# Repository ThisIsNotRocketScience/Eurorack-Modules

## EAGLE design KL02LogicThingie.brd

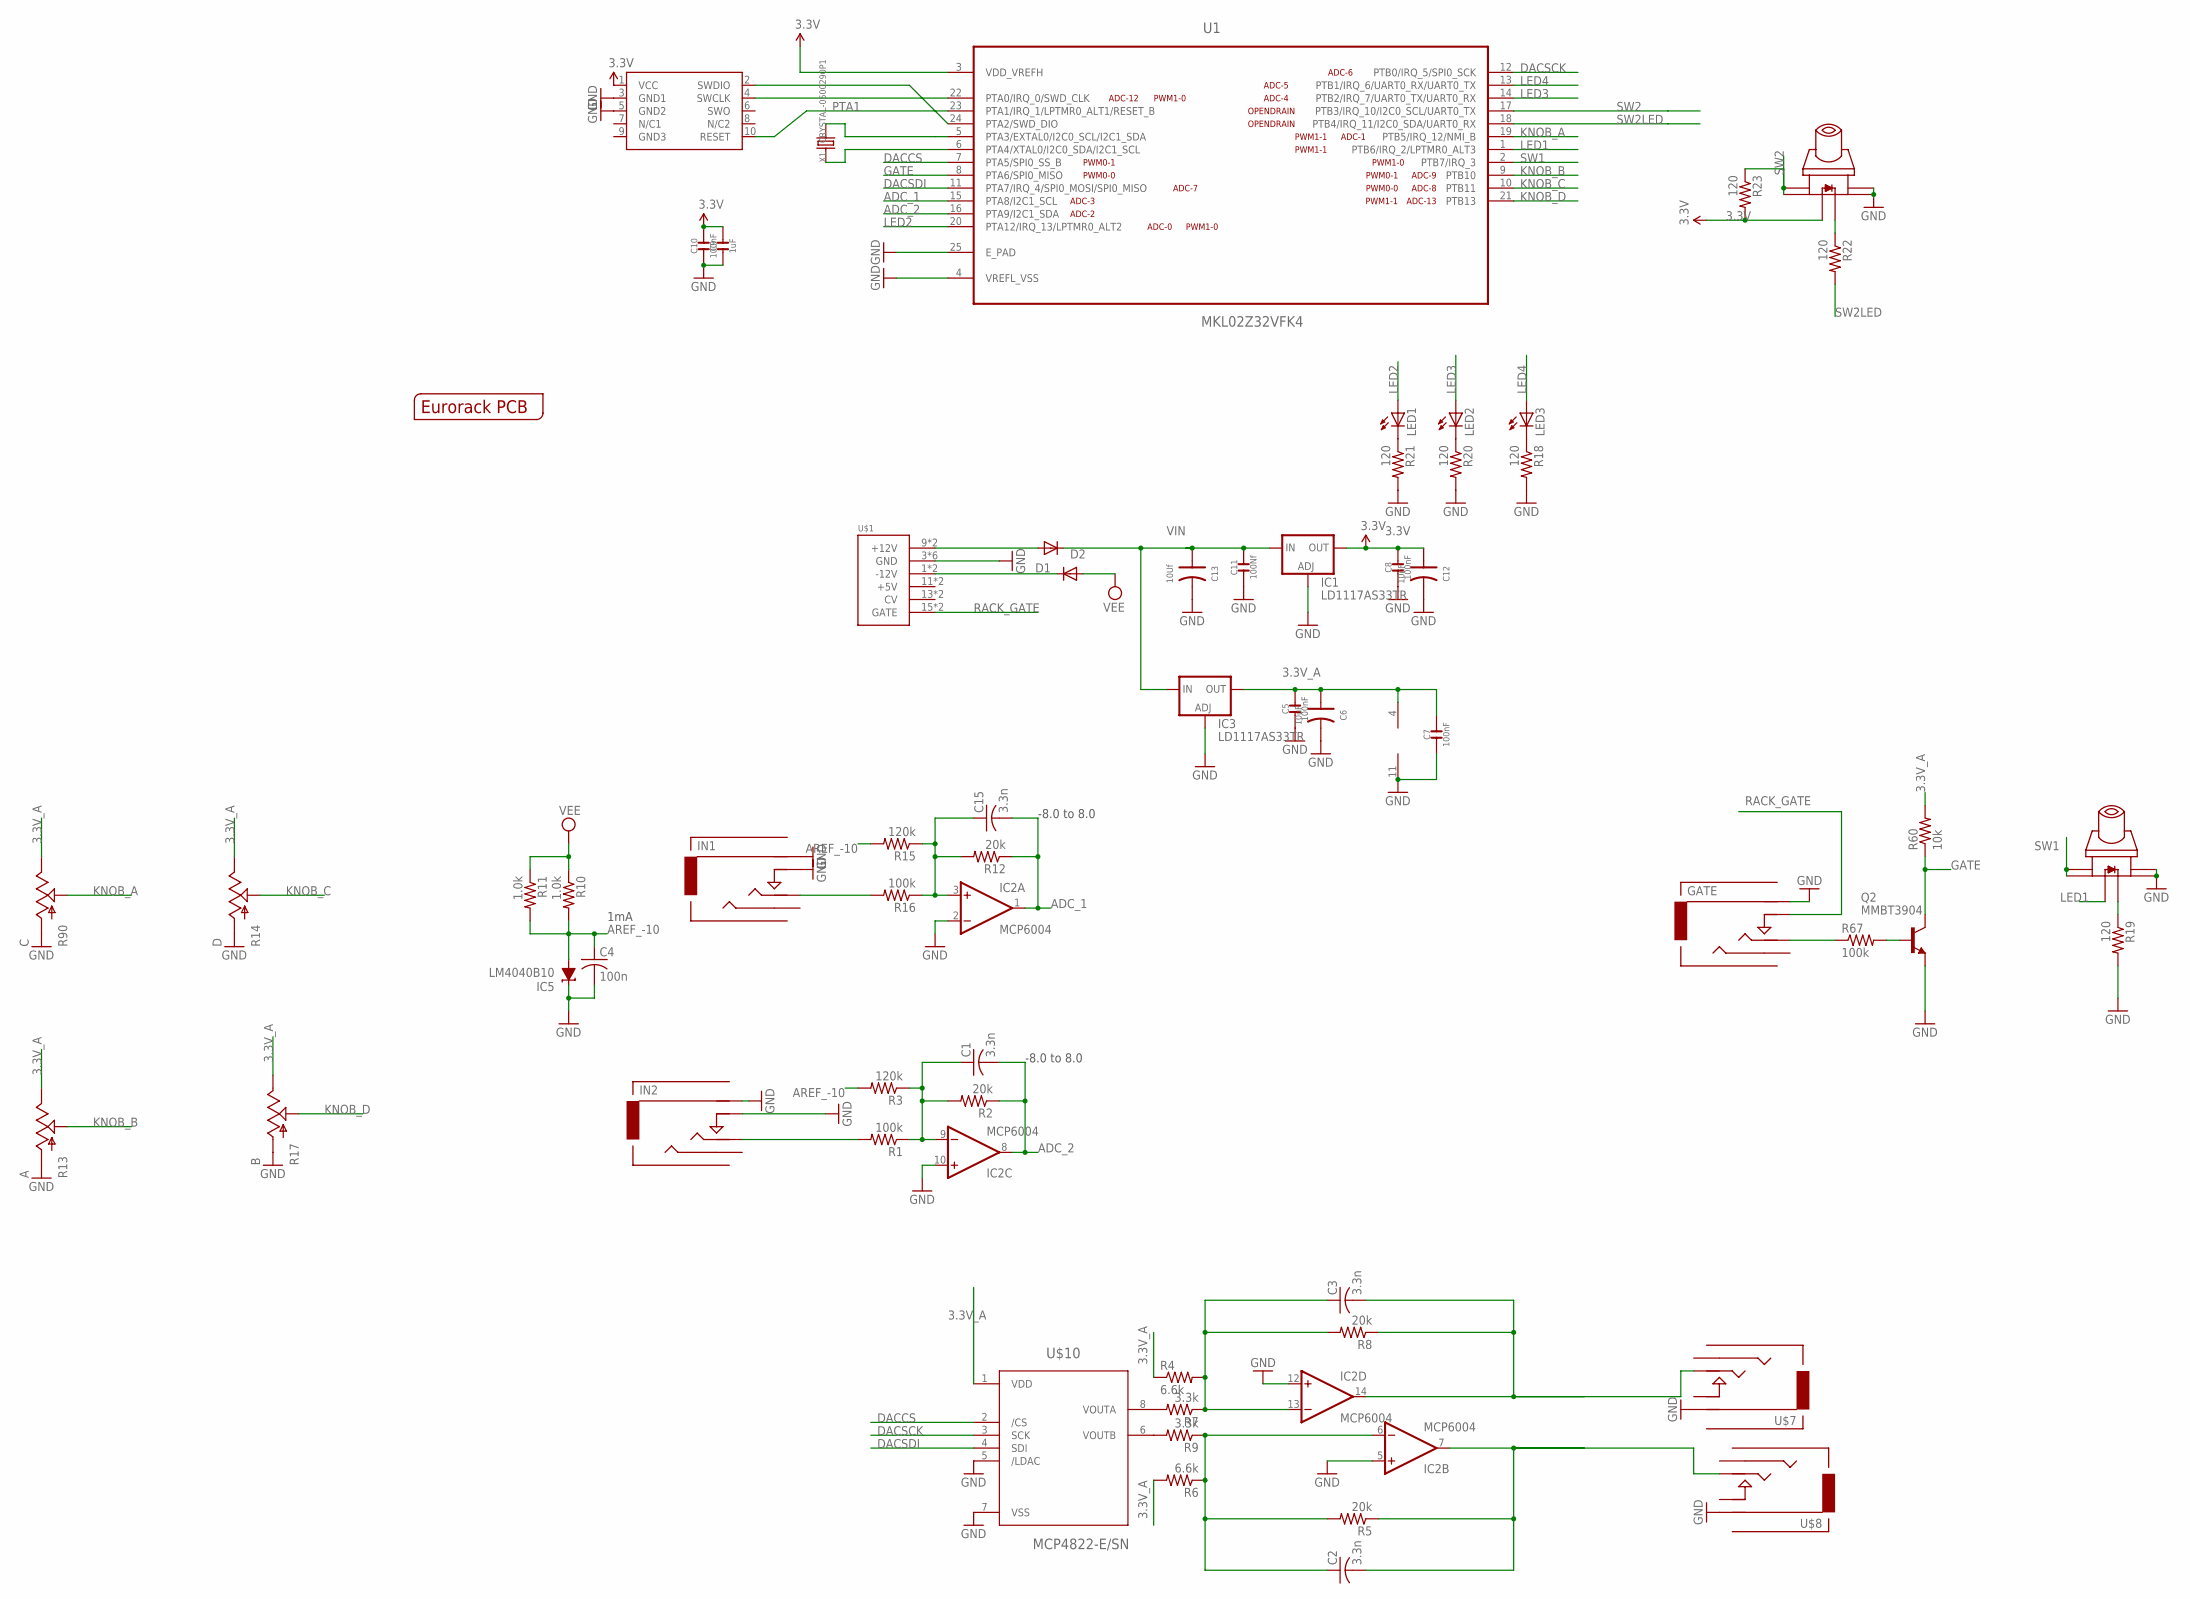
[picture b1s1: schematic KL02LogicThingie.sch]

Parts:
C1, C2, C3, C15: 3.3n; C0603
C4: 100n; C0603
C5, C7, C8, C10: 100nF; C0603
C6, C12: 10uF; AVX-A
C9: 1uF; C0603
C11: 100Nf; C0603
C13: 10Uf; AVX-A
D1, D2: 1N5819HW; SOD123
GATE: Gate; 3.5MM-JACK-SWITCH-13MM-INPUT
IC1, IC3: LD1117AS33TR; SOT223
IC2: MCP6004; SO14
IC5: LM4040B10; DBZ_R-PDSO-G3
IN1: In 2; 3.5MM-JACK-SWITCH-13MM-INPUT
IN2: In 1; 3.5MM-JACK-SWITCH-13MM-INPUT
LED1, LED2, LED3: LED3MM
Q2: MMBT3904; SOT23-BEC
R1, R16, R67: 100k; R0603
R2, R5, R8, R12: 20k; R0603
R3, R15: 120k; R0603
R4, R6: 6.6k; R0603
R7, R9: 3.3k; R0603
R10, R11: 1.0k; R0603
R13: A; OG-POTS_ALPS_POT_VERTICAL
R14: D; OG-POTS_ALPS_POT_VERTICAL
R17: B; OG-POTS_ALPS_POT_VERTICAL
R18, R19, R20, R21, R22, R23: 120; R0603
R60: 10k; R0603
R90: C; OG-POTS_ALPS_POT_VERTICAL
SWD1: CORTEX_SWD; M50-3600542
U1: MKL02Z32VFK4; QFN50P400X400X100-25N
U$1: POWER; POWER_16
U$2: EURORACK_PCB8HP; EURORACK8HPPCB
U$3, U$6: SWITCH_W_LED_PB6149L-X-102WHITE; PB6149L
U$7: Out 2; 3.5MM-JACK-SWITCH-13MM-OUTPUT
U$8: Out 1; 3.5MM-JACK-SWITCH-13MM-OUTPUT
U$10: MCP4822-E/SN; SOIC8-N_MC
X1: CRYSTAL-0500290P1; 2P-SMD-5.0X3.2

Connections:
3.3V: C8.2, C9.2, C10.2, C12.+ (1), IC1.2 (OUT), IC1.4 (OUT), R23.2, SWD1.1 (VCC), U1.3 (VDD_VREFH), U$3.LEDPOS (POS)
3.3V_A: C5.2, C6.+ (1), C7.2, IC2.4 (V+), IC3.2 (OUT), IC3.4 (OUT), R4.1, R6.2, R13.P$1 (E), R14.P$1 (E), R17.P$1 (E), R60.2, R90.P$1 (E), U$10.1 (VDD)
ADC_1: C15.2, IC2.1 (OUT), R12.1, U1.15 (PTA8/I2C1_SCL)
ADC_2: C1.2, IC2.8 (OUT), R2.1, U1.16 (PTA9/I2C1_SDA)
AREF_-10: C4.1, IC5.2 (A), R3.2, R10.2, R11.2, R15.2
DACCS: U1.7 (PTA5/SPI0_SS_B), U$10.2 (/CS)
DACSCK: U1.12 (PTB0/IRQ_5/SPI0_SCK), U$10.3 (SCK)
DACSDI: U1.11 (PTA7/IRQ_4/SPI0_MOSI/SPI0_MISO), U$10.4 (SDI)
GATE: Q2.C, R60.1, U1.8 (PTA6/SPI0_MISO)
GND: C4.2, C5.1, C6.- (2), C7.1, C8.1, C9.1, C10.1, C11.1, C12.- (2), C13.- (2), GATE.RING@1 (RING), GATE.RING@2 (RING), IC1.1 (ADJ), IC2.2 (-IN), IC2.5 (+IN), IC2.10 (+IN), IC2.11 (V-), IC2.12 (+IN), IC3.1 (ADJ), IC5.1 (C), IN1.RING@1 (RING), IN1.RING@2 (RING), IN1.SWITCH@1 (SWITCH), IN1.SWITCH@2 (SWITCH), IN2.RING@1 (RING), IN2.RING@2 (RING), IN2.SWITCH@1 (SWITCH), IN2.SWITCH@2 (SWITCH), Q2.E, R13.P$3 (A), R14.P$3 (A), R17.P$3 (A), R18.2, R19.2, R20.2, R21.2, R90.P$3 (A), SWD1.3 (GND1), SWD1.5 (GND2), U1.4 (VREFL_VSS), U1.25 (E_PAD), U$1.3 (GND), U$1.4 (GND), U$1.5 (GND), U$1.6 (GND), U$1.7 (GND), U$1.8 (GND), U$3.3, U$3.4, U$6.3, U$6.4, U$7.RING@1 (RING), U$7.RING@2 (RING), U$8.RING@1 (RING), U$8.RING@2 (RING), U$10.5 (/LDAC), U$10.7 (VSS)
KNOB_A: R90.P$2 (S), U1.19 (PTB5/IRQ_12/NMI_B)
KNOB_B: R13.P$2 (S), U1.9 (PTB10)
KNOB_C: R14.P$2 (S), U1.10 (PTB11)
KNOB_D: R17.P$2 (S), U1.21 (PTB13)
LED1: U1.1 (PTB6/IRQ_2/LPTMR0_ALT3), U$6.LEDPOS (POS)
LED2: LED1.A, U1.20 (PTA12/IRQ_13/LPTMR0_ALT2)
LED3: LED2.A, U1.14 (PTB2/IRQ_7/UART0_TX/UART0_RX)
LED4: LED3.A, U1.13 (PTB1/IRQ_6/UART0_RX/UART0_TX)
unnamed: U1.5 (PTA3/EXTAL0/I2C0_SCL/I2C1_SDA), X1.2
unnamed: U1.6 (PTA4/XTAL0/I2C0_SDA/I2C1_SCL), X1.1
unnamed: IN1.TIP@1 (TIP), IN1.TIP@2 (TIP), R16.2
unnamed: C15.1, IC2.3 (+IN), R12.2, R15.1, R16.1
unnamed: SWD1.4 (SWCLK), U1.22 (PTA0/IRQ_0/SWD_CLK)
unnamed: IN2.TIP@1 (TIP), IN2.TIP@2 (TIP), R1.2
unnamed: SWD1.2 (SWDIO), U1.24 (PTA2/SWD_DIO)
unnamed: C1.1, IC2.9 (-IN), R1.1, R2.2, R3.1
unnamed: C2.1, IC2.6 (-IN), R5.2, R6.1, R9.1
unnamed: C3.1, IC2.13 (-IN), R4.2, R7.1, R8.2
unnamed: R7.2, U$10.8 (VOUTA)
unnamed: R9.2, U$10.6 (VOUTB)
unnamed: D1.A, U$1.9 (+12V), U$1.10 (+12V)
unnamed: R19.1, U$6.LEDNEG (NEG)
unnamed: LED3.K (C), R18.1
unnamed: LED2.K (C), R20.1
unnamed: LED1.K (C), R21.1
unnamed: C3.2, IC2.14 (OUT), R8.1, U$7.TIP@1 (TIP), U$7.TIP@2 (TIP)
unnamed: R22.1, U$3.LEDNEG (NEG)
unnamed: C2.2, IC2.7 (OUT), R5.1, U$8.TIP@1 (TIP), U$8.TIP@2 (TIP)
unnamed: GATE.TIP@1 (TIP), GATE.TIP@2 (TIP), R67.1
unnamed: D2.C, U$1.1 (-12V), U$1.2 (-12V)
unnamed: Q2.B, R67.2
PTA1: SWD1.10 (RESET), U1.23 (PTA1/IRQ_1/LPTMR0_ALT1/RESET_B)
RACK_GATE: GATE.SWITCH@1 (SWITCH), GATE.SWITCH@2 (SWITCH), U$1.15 (GATE), U$1.16 (GATE)
SW1: U1.2 (PTB7/IRQ_3), U$6.1, U$6.2
SW2: R23.1, U1.17 (PTB3/IRQ_10/I2C0_SCL/UART0_TX), U$3.1, U$3.2
SW2LED: R22.2, U1.18 (PTB4/IRQ_11/I2C0_SDA/UART0_RX)
VEE: D2.A, R10.1, R11.1
VIN: C11.2, C13.+ (1), D1.C, IC1.3 (IN), IC3.3 (IN)

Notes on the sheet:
-8.0 to 8.0
1mA

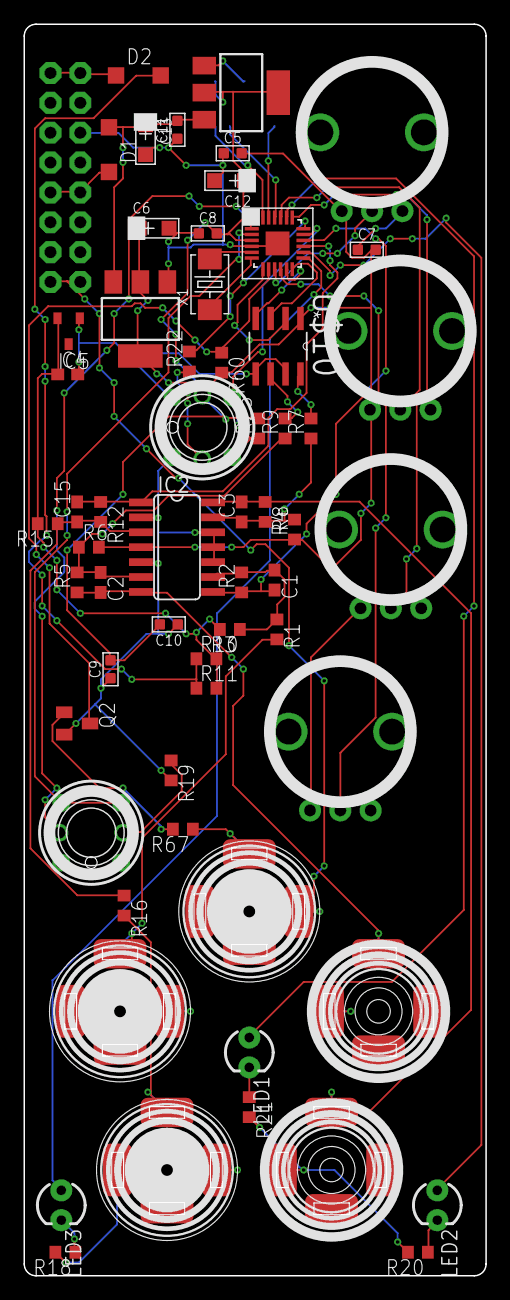
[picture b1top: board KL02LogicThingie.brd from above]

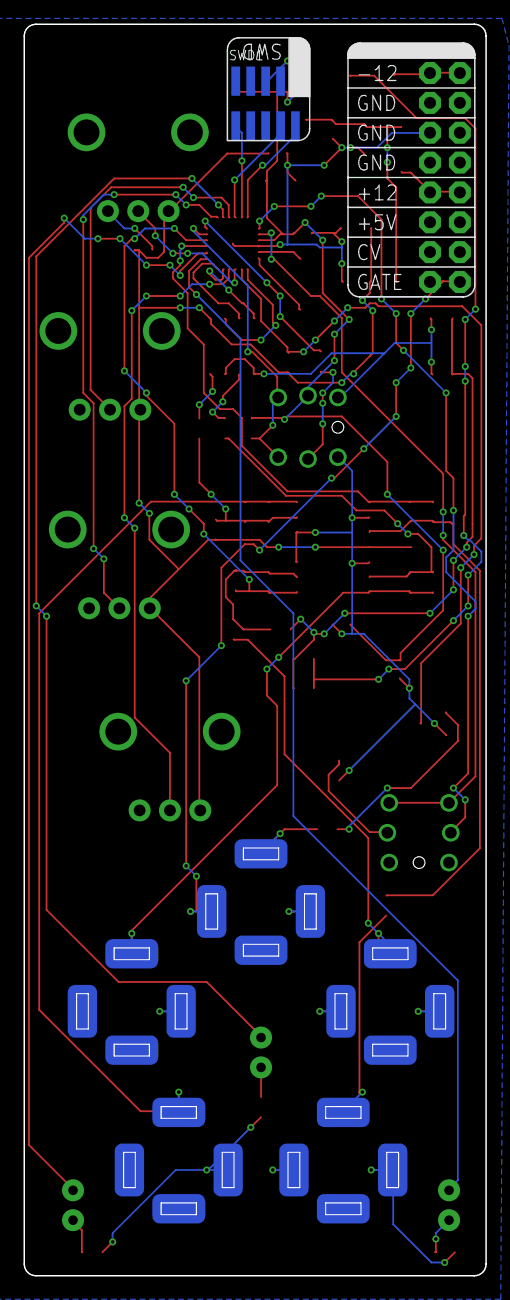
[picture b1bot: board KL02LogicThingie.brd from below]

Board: 2 copper layers, 39.3 x 106.5 mm, 63 parts (2 on the bottom side), 48 nets.

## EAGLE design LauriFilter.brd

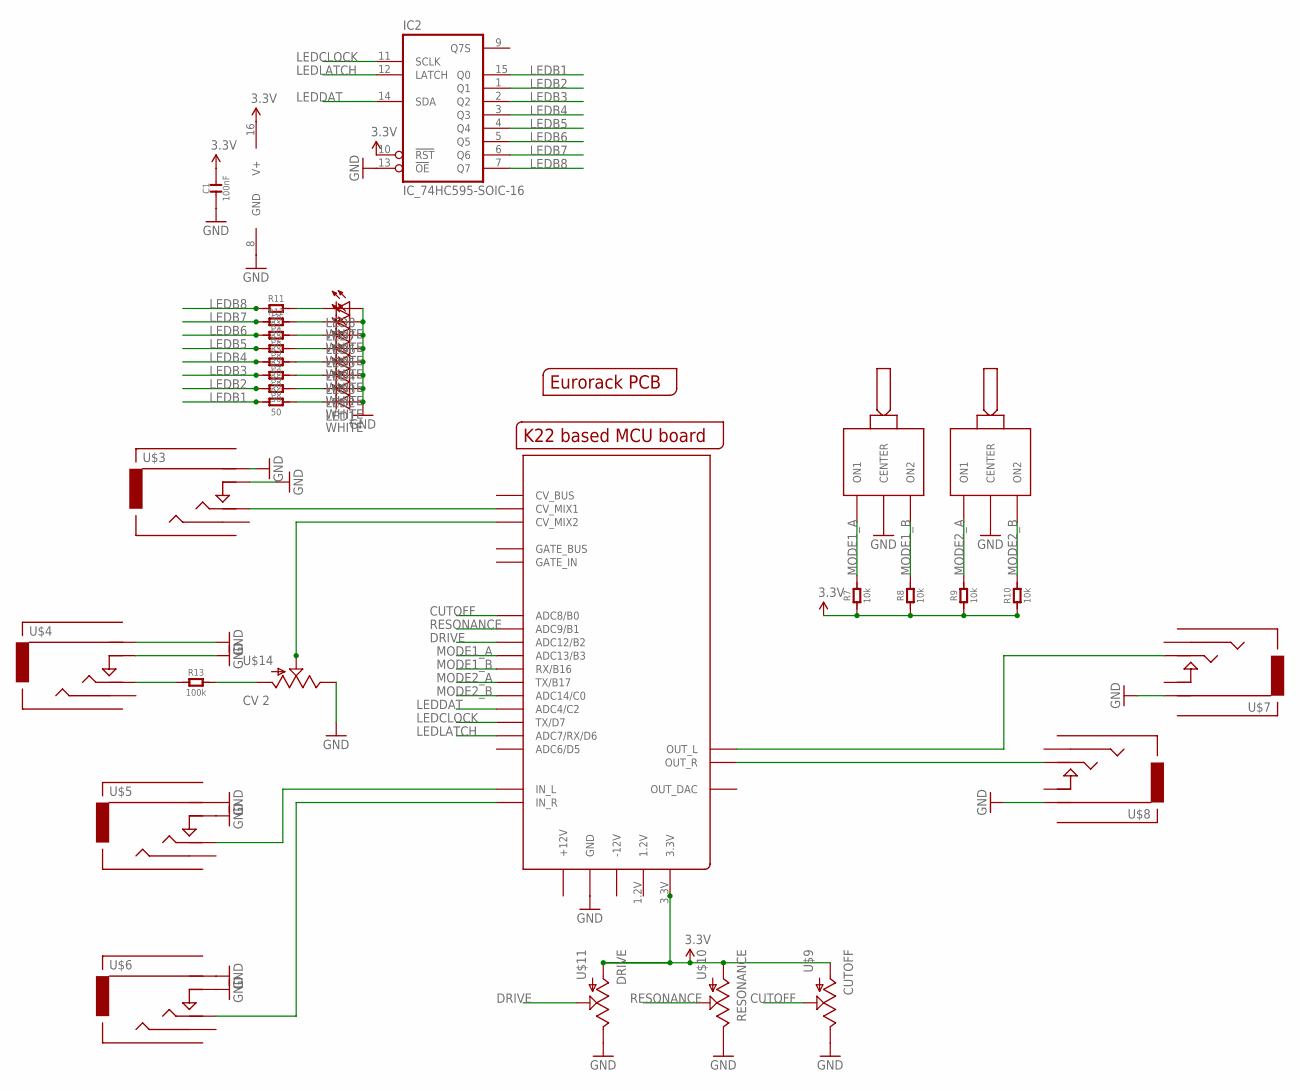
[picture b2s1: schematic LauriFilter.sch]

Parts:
C1: 100nF; C0603
IC2: IC_74HC595-SOIC-16; SOIC-16
LED1, LED2, LED3, LED4, LED5, LED6, LED7, LED8: WHITE; LED3MM
R1, R2, R3, R4, R5, R6, R11, R12: 50; R0603
R7, R8, R9, R10: 10k; R0603
R13: 100k; R0603
U$1: MCUBOARD; MCUBASEBOARD
U$2: EURORACK_PCB8HP; EURORACK8HPPCB
U$3: CV 1; 3.5MM-JACK-SWITCH-13MM-INPUT
U$4: CV 2; 3.5MM-JACK-SWITCH-13MM-INPUT
U$5: IN 1; 3.5MM-JACK-SWITCH-13MM-INPUT
U$6: IN 2; 3.5MM-JACK-SWITCH-13MM-INPUT
U$7: OUT 1; 3.5MM-JACK-SWITCH-13MM-OUTPUT
U$8: OUT 2; 3.5MM-JACK-SWITCH-13MM-OUTPUT
U$9: CUTOFF; OG-POTS_ALPS_POT_VERTICAL
U$10: RESONANCE; OG-POTS_ALPS_POT_VERTICAL
U$11: DRIVE; OG-POTS_ALPS_POT_VERTICAL
U$12, U$13: ONOFFON; MULTICOMP1MS-ONOFFON
U$14: CV 2; OG-POTS_ALPS_POT_VERTICAL

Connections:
3.3V: C1.2, IC2.10 (!RST), IC2.16 (V+), R7.1, R8.1, R9.1, R10.1, U$1.3.3V, U$9.P$3 (A), U$10.P$3 (A), U$11.P$3 (A)
CUTOFF: U$1.ADC8 (ADC8/B0), U$9.P$2 (S)
DRIVE: U$1.ADC12 (ADC12/B2), U$11.P$2 (S)
GND: C1.1, IC2.8 (GND), IC2.13 (!OE), LED1.A, LED2.A, LED3.A, LED4.A, LED5.A, LED6.A, LED7.A, LED8.A, U$1.GND@1 (GND), U$1.GND@2 (GND), U$1.GND@4 (GND), U$1.GND@5 (GND), U$1.GND@6 (GND), U$1.GND@7 (GND), U$1.GND@8 (GND), U$1.GND@9 (GND), U$1.GND_BUS (GND), U$3.RING@1 (RING), U$3.RING@2 (RING), U$3.SWITCH@1 (SWITCH), U$3.SWITCH@2 (SWITCH), U$4.RING@1 (RING), U$4.RING@2 (RING), U$4.SWITCH@1 (SWITCH), U$4.SWITCH@2 (SWITCH), U$5.RING@1 (RING), U$5.RING@2 (RING), U$5.SWITCH@1 (SWITCH), U$5.SWITCH@2 (SWITCH), U$6.RING@1 (RING), U$6.RING@2 (RING), U$6.SWITCH@1 (SWITCH), U$6.SWITCH@2 (SWITCH), U$7.RING@1 (RING), U$7.RING@2 (RING), U$8.RING@1 (RING), U$8.RING@2 (RING), U$9.P$1 (E), U$10.P$1 (E), U$11.P$1 (E), U$12.2 (CENTER), U$13.2 (CENTER), U$14.P$1 (E)
LEDB1: IC2.15 (Q0), R6.1
LEDB2: IC2.1 (Q1), R5.1
LEDB3: IC2.2 (Q2), R4.1
LEDB4: IC2.3 (Q3), R3.1
LEDB5: IC2.4 (Q4), R2.1
LEDB6: IC2.5 (Q5), R1.1
LEDB7: IC2.6 (Q6), R12.1
LEDB8: IC2.7 (Q7), R11.1
LEDCLOCK: IC2.11 (SCLK), U$1.TX/D7
LEDDAT: IC2.14 (SDA), U$1.ADC4 (ADC4/C2)
LEDLATCH: IC2.12 (LATCH), U$1.ADC7 (ADC7/RX/D6)
MODE1_A: R7.2, U$1.ADC13 (ADC13/B3), U$12.1 (ON1)
MODE1_B: R8.2, U$1.RX/B16, U$12.3 (ON2)
MODE2_A: R9.2, U$1.TX/B17, U$13.1 (ON1)
MODE2_B: R10.2, U$1.ADC14 (ADC14/C0), U$13.3 (ON2)
unnamed: U$1.IN_L, U$5.TIP@1 (TIP), U$5.TIP@2 (TIP)
unnamed: U$1.IN_R, U$6.TIP@1 (TIP), U$6.TIP@2 (TIP)
unnamed: U$1.CV_MIX1, U$3.TIP@1 (TIP), U$3.TIP@2 (TIP)
unnamed: U$1.CV_MIX2, U$14.P$2 (S)
unnamed: U$1.OUT_L, U$7.TIP@1 (TIP), U$7.TIP@2 (TIP)
unnamed: U$1.OUT_R, U$8.TIP@1 (TIP), U$8.TIP@2 (TIP)
unnamed: R13.1, U$4.TIP@1 (TIP), U$4.TIP@2 (TIP)
unnamed: LED8.K (C), R11.2
unnamed: LED7.K (C), R12.2
unnamed: R13.2, U$14.P$3 (A)
unnamed: LED6.K (C), R1.2
unnamed: LED5.K (C), R2.2
unnamed: LED4.K (C), R3.2
unnamed: LED3.K (C), R4.2
unnamed: LED2.K (C), R5.2
unnamed: LED1.K (C), R6.2
RESONANCE: U$1.ADC9 (ADC9/B1), U$10.P$2 (S)

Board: 2 copper layers, 37 parts (15 on the bottom side), 36 nets, no tracks yet.

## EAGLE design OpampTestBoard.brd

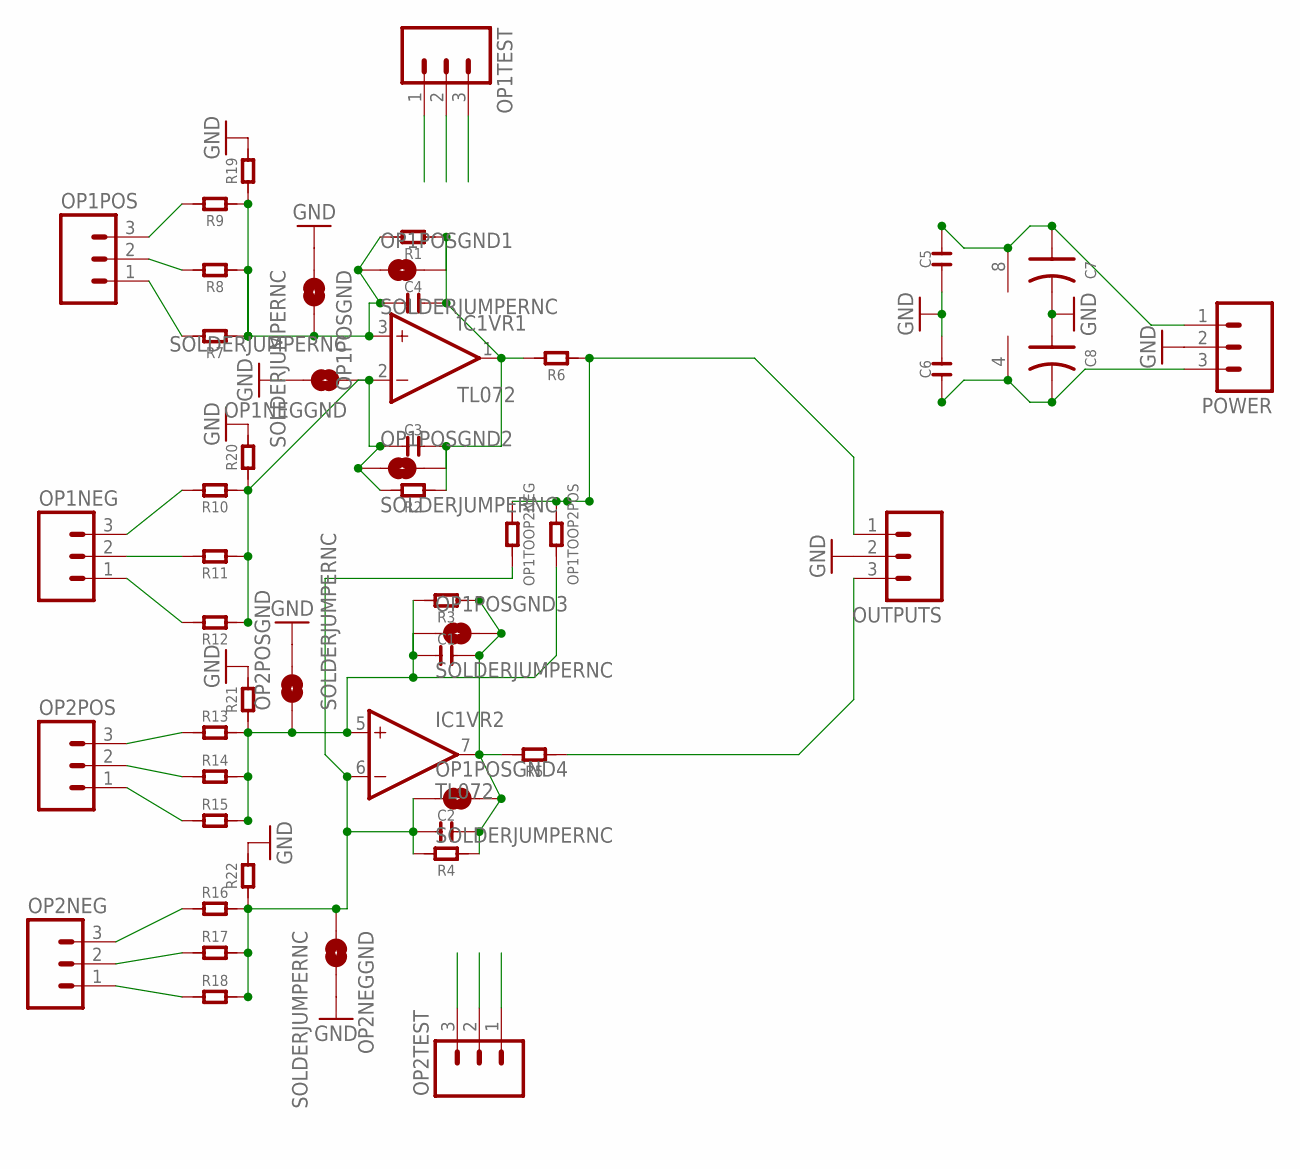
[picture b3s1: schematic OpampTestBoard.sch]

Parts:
C1, C2, C3, C4, C5, C6: C-0805; C0805
C7, C8: C-POLAR-A; AVX-A
IC1: TL072; SO08
OP1NEG, OP1POS, OP1TEST, OP2NEG, OP2POS, OP2TEST: M03PTH; 1X03
OP1NEGGND, OP1POSGND, OP1POSGND1, OP1POSGND2, OP1POSGND3, OP1POSGND4, OP2NEGGND, OP2POSGND: SOLDERJUMPERNC; SJ_2S
OP1TOOP2NEG, OP1TOOP2POS: R-0603; R0603
OUTPUTS: M03PTH; 1X03
POWER: M03PTH; 1X03
R1, R2, R3, R4, R5, R6, R7, R8, R9, R10, R11, R12, R13, R14, R15, R16, R17, R18, R19, R20, R21, R22: R-0603; R0603

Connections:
GND: C5.1, C6.2, C7.- (2), C8.+ (1), OP1NEGGND.2, OP1POSGND.1, OP2NEGGND.2, OP2POSGND.2, OUTPUTS.2, POWER.2, R19.2, R20.2, R21.2, R22.2
unnamed: OP1POS.3, R9.2
unnamed: OP1TOOP2NEG.1, OP1TOOP2POS.1, OUTPUTS.1, R6.1
unnamed: OP1POS.2, R8.2
unnamed: OUTPUTS.3, R5.1
unnamed: C6.1, C8.- (2), IC1.4 (V-), POWER.3
unnamed: C5.2, C7.+ (1), IC1.8 (V+), POWER.1
unnamed: OP1POS.1, R7.2
unnamed: OP1NEG.3, R10.2
unnamed: OP1NEG.2, R11.2
unnamed: OP1NEG.1, R12.2
unnamed: OP2POS.3, R13.1
unnamed: OP2POS.2, R14.1
unnamed: OP2POS.1, R15.1
unnamed: OP2NEG.3, R16.1
unnamed: OP2NEG.2, R17.1
unnamed: OP2NEG.1, R18.1
OP1NEG: C3.1, IC1.2 (-IN), OP1NEGGND.1, OP1POSGND2.1, OP1TEST.1, R2.2, R10.1, R11.1, R12.1, R20.1
OP1OUT: C3.2, C4.2, IC1.1 (OUT), OP1POSGND1.2, OP1POSGND2.2, OP1TEST.3, R1.1, R2.1, R6.2
OP1POS: C4.1, IC1.3 (+IN), OP1POSGND.2, OP1POSGND1.1, OP1TEST.2, R1.2, R7.1, R8.1, R9.1, R19.1
OP2NEG: C2.1, IC1.6 (-IN), OP1POSGND4.1, OP1TOOP2NEG.2, OP2NEGGND.1, OP2TEST.3, R4.2, R16.2, R17.2, R18.2, R22.1
OP2OUT: C1.2, C2.2, IC1.7 (OUT), OP1POSGND3.2, OP1POSGND4.2, OP2TEST.2, R3.1, R4.1, R5.2
OP2POS: C1.1, IC1.5 (+IN), OP1POSGND3.1, OP1TOOP2POS.2, OP2POSGND.1, OP2TEST.1, R3.2, R13.2, R14.2, R15.2, R21.1

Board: 2 copper layers, 49 parts (0 on the bottom side), 23 nets, no tracks yet.

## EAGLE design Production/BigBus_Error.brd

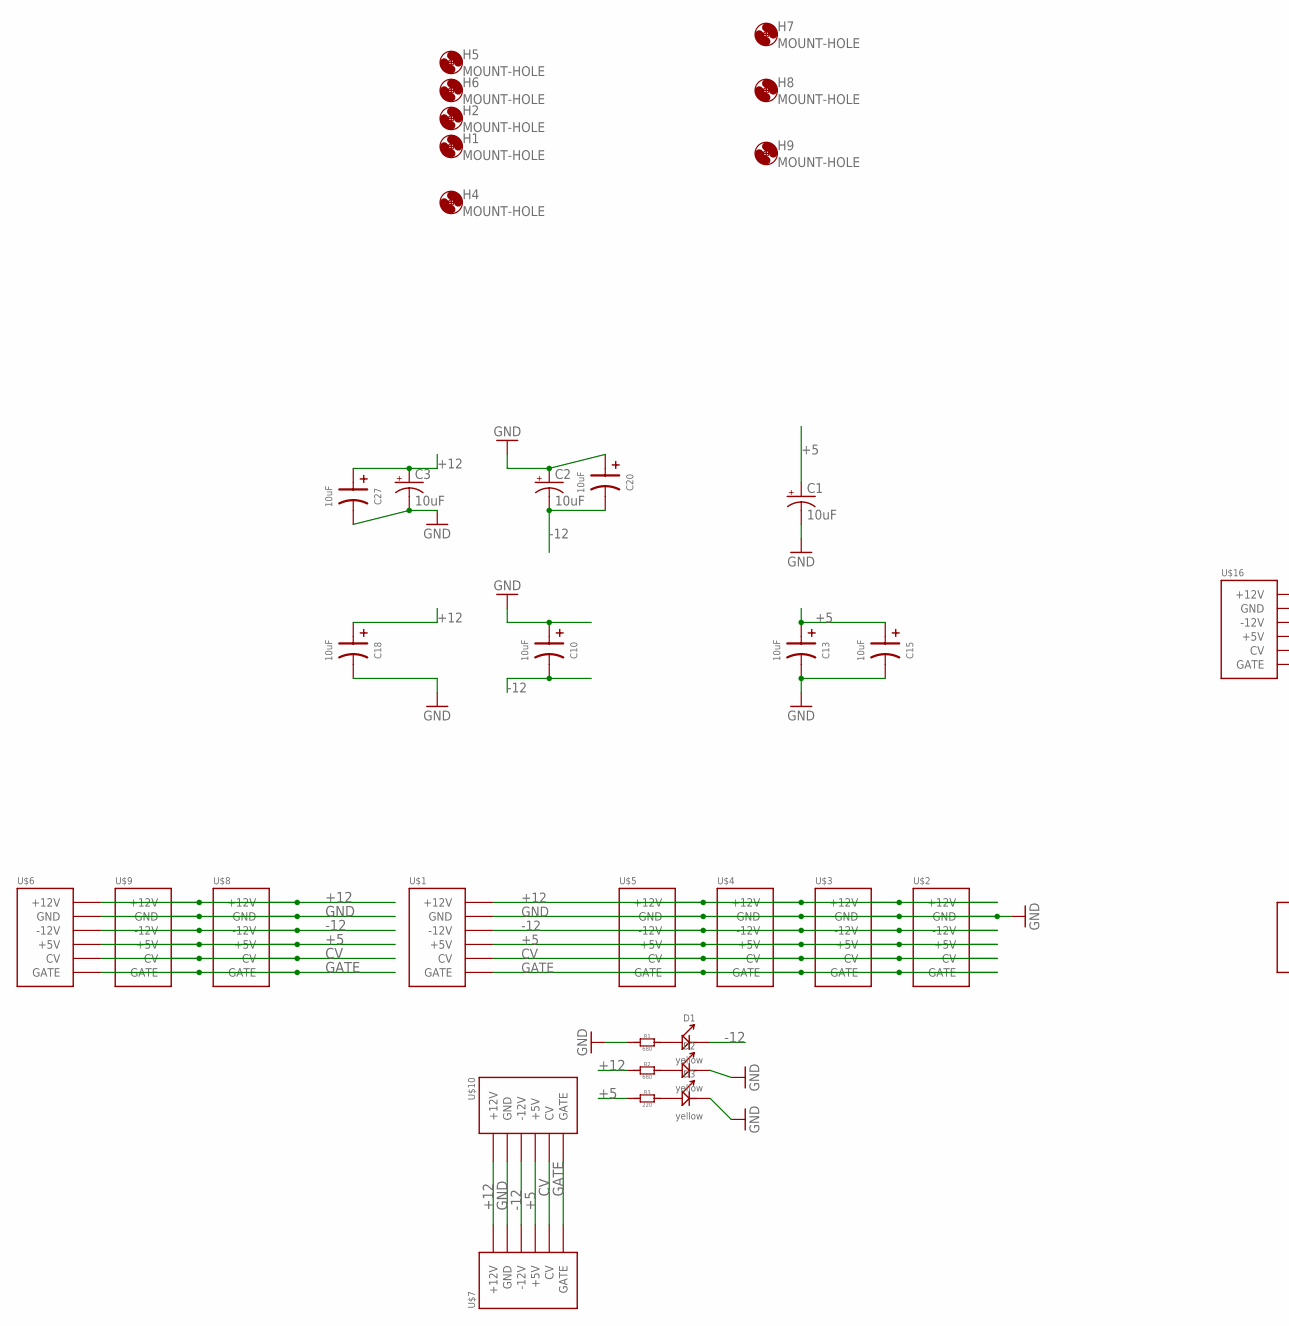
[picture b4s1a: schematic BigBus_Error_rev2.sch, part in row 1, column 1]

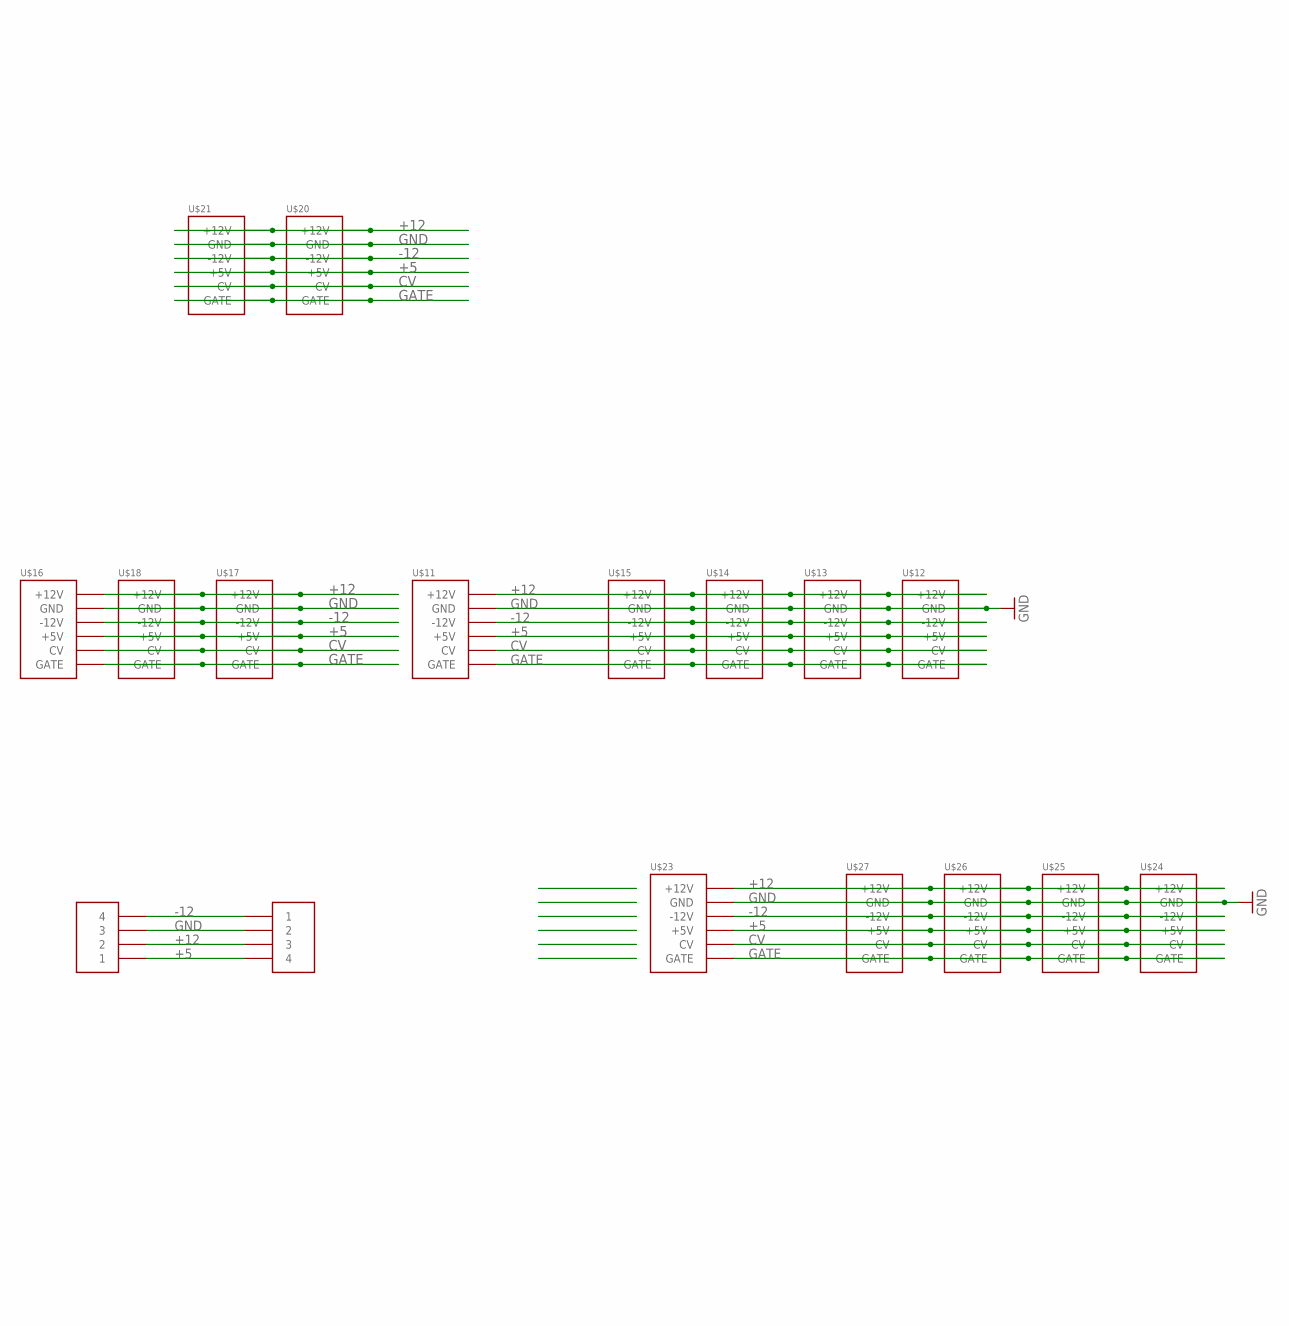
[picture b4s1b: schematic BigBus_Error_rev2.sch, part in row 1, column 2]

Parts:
C1, C2, C3: 10uF; PANASONIC_D
C10, C13, C15, C18, C20, C27: 10uF; CASE-A_3216
D1, D2, D3: yellow; LED0603
H1, H2, H4, H5, H6, H7, H8, H9: MOUNT-HOLE; 3.2-NOMARKINGS-SMALLSAFEZONE
R1, R2: 680; R0603
R3: 220; R0603
U$1, U$2, U$3, U$4, U$5, U$6, U$7, U$8, U$9, U$10, U$11, U$12, U$13, U$14, U$15, U$16, U$17, U$18, U$20, U$21, U$23, U$24, U$25, U$26, U$27: POWER_SHROUDED_NOTEXT; POWER_16_SHROUDED_NOTEXT
U$19, U$22: 4PIN5MM

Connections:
+5: C1.+, C13.+ (1), C15.+ (1), R3.1, U$1.11 (+5V), U$1.12 (+5V), U$2.11 (+5V), U$2.12 (+5V), U$3.11 (+5V), U$3.12 (+5V), U$4.11 (+5V), U$4.12 (+5V), U$5.11 (+5V), U$5.12 (+5V), U$6.11 (+5V), U$6.12 (+5V), U$7.11 (+5V), U$7.12 (+5V), U$8.11 (+5V), U$8.12 (+5V), U$9.11 (+5V), U$9.12 (+5V), U$10.11 (+5V), U$10.12 (+5V), U$11.11 (+5V), U$11.12 (+5V), U$12.11 (+5V), U$12.12 (+5V), U$13.11 (+5V), U$13.12 (+5V), U$14.11 (+5V), U$14.12 (+5V), U$15.11 (+5V), U$15.12 (+5V), U$16.11 (+5V), U$16.12 (+5V), U$17.11 (+5V), U$17.12 (+5V), U$18.11 (+5V), U$18.12 (+5V), U$19.4, U$20.11 (+5V), U$20.12 (+5V), U$21.11 (+5V), U$21.12 (+5V), U$22.1, U$23.11 (+5V), U$24.11 (+5V), U$25.11 (+5V), U$26.11 (+5V), U$27.11 (+5V)
+12: C3.+, C18.+ (1), C27.+ (1), R2.1, U$1.9 (+12V), U$1.10 (+12V), U$2.9 (+12V), U$2.10 (+12V), U$3.9 (+12V), U$3.10 (+12V), U$4.9 (+12V), U$4.10 (+12V), U$5.9 (+12V), U$5.10 (+12V), U$6.9 (+12V), U$6.10 (+12V), U$7.9 (+12V), U$7.10 (+12V), U$8.9 (+12V), U$8.10 (+12V), U$9.9 (+12V), U$9.10 (+12V), U$10.9 (+12V), U$10.10 (+12V), U$11.9 (+12V), U$11.10 (+12V), U$12.9 (+12V), U$12.10 (+12V), U$13.9 (+12V), U$13.10 (+12V), U$14.9 (+12V), U$14.10 (+12V), U$15.9 (+12V), U$15.10 (+12V), U$16.9 (+12V), U$16.10 (+12V), U$17.9 (+12V), U$17.10 (+12V), U$18.9 (+12V), U$18.10 (+12V), U$19.3, U$20.9 (+12V), U$20.10 (+12V), U$21.9 (+12V), U$21.10 (+12V), U$22.2, U$23.9 (+12V), U$24.9 (+12V), U$25.9 (+12V), U$26.9 (+12V), U$27.9 (+12V)
-12: C2.-, C10.- (2), C20.- (2), D1.-, U$1.1 (-12V), U$1.2 (-12V), U$2.1 (-12V), U$2.2 (-12V), U$3.1 (-12V), U$3.2 (-12V), U$4.1 (-12V), U$4.2 (-12V), U$5.1 (-12V), U$5.2 (-12V), U$6.1 (-12V), U$6.2 (-12V), U$7.1 (-12V), U$7.2 (-12V), U$8.1 (-12V), U$8.2 (-12V), U$9.1 (-12V), U$9.2 (-12V), U$10.1 (-12V), U$10.2 (-12V), U$11.1 (-12V), U$11.2 (-12V), U$12.1 (-12V), U$12.2 (-12V), U$13.1 (-12V), U$13.2 (-12V), U$14.1 (-12V), U$14.2 (-12V), U$15.1 (-12V), U$15.2 (-12V), U$16.1 (-12V), U$16.2 (-12V), U$17.1 (-12V), U$17.2 (-12V), U$18.1 (-12V), U$18.2 (-12V), U$19.1, U$20.1 (-12V), U$20.2 (-12V), U$21.1 (-12V), U$21.2 (-12V), U$22.4, U$23.1 (-12V), U$24.1 (-12V), U$25.1 (-12V), U$26.1 (-12V), U$27.1 (-12V)
CV: U$1.13 (CV), U$1.14 (CV), U$2.13 (CV), U$2.14 (CV), U$3.13 (CV), U$3.14 (CV), U$4.13 (CV), U$4.14 (CV), U$5.13 (CV), U$5.14 (CV), U$6.13 (CV), U$6.14 (CV), U$7.13 (CV), U$7.14 (CV), U$8.13 (CV), U$8.14 (CV), U$9.13 (CV), U$9.14 (CV), U$10.13 (CV), U$10.14 (CV), U$11.13 (CV), U$11.14 (CV), U$12.13 (CV), U$12.14 (CV), U$13.13 (CV), U$13.14 (CV), U$14.13 (CV), U$14.14 (CV), U$15.13 (CV), U$15.14 (CV), U$16.13 (CV), U$16.14 (CV), U$17.13 (CV), U$17.14 (CV), U$18.13 (CV), U$18.14 (CV), U$20.13 (CV), U$20.14 (CV), U$21.13 (CV), U$21.14 (CV), U$23.13 (CV), U$24.13 (CV), U$25.13 (CV), U$26.13 (CV), U$27.13 (CV)
GATE: U$1.15 (GATE), U$1.16 (GATE), U$2.15 (GATE), U$2.16 (GATE), U$3.15 (GATE), U$3.16 (GATE), U$4.15 (GATE), U$4.16 (GATE), U$5.15 (GATE), U$5.16 (GATE), U$6.15 (GATE), U$6.16 (GATE), U$7.15 (GATE), U$7.16 (GATE), U$8.15 (GATE), U$8.16 (GATE), U$9.15 (GATE), U$9.16 (GATE), U$10.15 (GATE), U$10.16 (GATE), U$11.15 (GATE), U$11.16 (GATE), U$12.15 (GATE), U$12.16 (GATE), U$13.15 (GATE), U$13.16 (GATE), U$14.15 (GATE), U$14.16 (GATE), U$15.15 (GATE), U$15.16 (GATE), U$16.15 (GATE), U$16.16 (GATE), U$17.15 (GATE), U$17.16 (GATE), U$18.15 (GATE), U$18.16 (GATE), U$20.15 (GATE), U$20.16 (GATE), U$21.15 (GATE), U$21.16 (GATE), U$23.15 (GATE), U$24.15 (GATE), U$25.15 (GATE), U$26.15 (GATE), U$27.15 (GATE)
GND: C1.-, C2.+, C3.-, C10.+ (1), C13.- (2), C15.- (2), C18.- (2), C20.+ (1), C27.- (2), D2.-, D3.-, R1.1, U$1.3 (GND), U$1.4 (GND), U$1.5 (GND), U$1.6 (GND), U$1.7 (GND), U$1.8 (GND), U$2.3 (GND), U$2.4 (GND), U$2.5 (GND), U$2.6 (GND), U$2.7 (GND), U$2.8 (GND), U$3.3 (GND), U$3.4 (GND), U$3.5 (GND), U$3.6 (GND), U$3.7 (GND), U$3.8 (GND), U$4.3 (GND), U$4.4 (GND), U$4.5 (GND), U$4.6 (GND), U$4.7 (GND), U$4.8 (GND), U$5.3 (GND), U$5.4 (GND), U$5.5 (GND), U$5.6 (GND), U$5.7 (GND), U$5.8 (GND), U$6.3 (GND), U$6.4 (GND), U$6.5 (GND), U$6.6 (GND), U$6.7 (GND), U$6.8 (GND), U$7.3 (GND), U$7.4 (GND), U$7.5 (GND), U$7.6 (GND), U$7.7 (GND), U$7.8 (GND), U$8.3 (GND), U$8.4 (GND), U$8.5 (GND), U$8.6 (GND), U$8.7 (GND), U$8.8 (GND), U$9.3 (GND), U$9.4 (GND), U$9.5 (GND), U$9.6 (GND), U$9.7 (GND), U$9.8 (GND), U$10.3 (GND), U$10.4 (GND), U$10.5 (GND), U$10.6 (GND), U$10.7 (GND), U$10.8 (GND), U$11.3 (GND), U$11.4 (GND), U$11.5 (GND), U$11.6 (GND), U$11.7 (GND), U$11.8 (GND), U$12.3 (GND), U$12.4 (GND), U$12.5 (GND), U$12.6 (GND), U$12.7 (GND), U$12.8 (GND), U$13.3 (GND), U$13.4 (GND), U$13.5 (GND), U$13.6 (GND), U$13.7 (GND), U$13.8 (GND), U$14.3 (GND), U$14.4 (GND), U$14.5 (GND), U$14.6 (GND), U$14.7 (GND), U$14.8 (GND), U$15.3 (GND), U$15.4 (GND), U$15.5 (GND), U$15.6 (GND), U$15.7 (GND), U$15.8 (GND), U$16.3 (GND), U$16.4 (GND), U$16.5 (GND), U$16.6 (GND), U$16.7 (GND), U$16.8 (GND), U$17.3 (GND), U$17.4 (GND), U$17.5 (GND), U$17.6 (GND), U$17.7 (GND), U$17.8 (GND), U$18.3 (GND), U$18.4 (GND), U$18.5 (GND), U$18.6 (GND), U$18.7 (GND), U$18.8 (GND), U$19.2, U$20.3 (GND), U$20.4 (GND), U$20.5 (GND), U$20.6 (GND), U$20.7 (GND), U$20.8 (GND), U$21.3 (GND), U$21.4 (GND), U$21.5 (GND), U$21.6 (GND), U$21.7 (GND), U$21.8 (GND), U$22.3, U$23.3 (GND), U$24.3 (GND), U$25.3 (GND), U$26.3 (GND), U$27.3 (GND)
unnamed: D1.+, R1.2
unnamed: D2.+, R2.2
unnamed: D3.+, R3.2

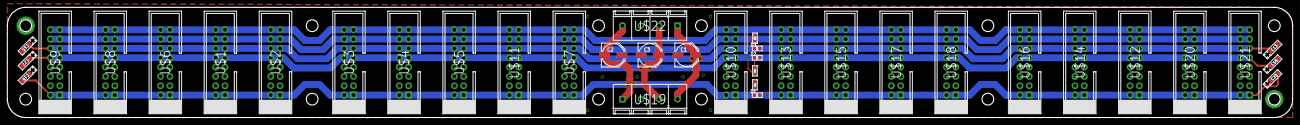
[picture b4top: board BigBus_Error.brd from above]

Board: 2 copper layers, 350.0 x 30.0 mm, 47 parts (0 on the bottom side), 9 nets.

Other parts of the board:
H11, H12: MOUNT-HOLE; 3.2-NOMARKINGS-SMALLSAFEZONE

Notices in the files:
parts and their libraries:
SparkFun-LED: Licensing: CC v3.0 Share-Alike You are welcome to use this library for commercial purposes.
